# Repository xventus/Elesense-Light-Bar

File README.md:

# LAMP

Elesense Light Bar is a monitor lamp from [kickstarter](https://www.kickstarter.com/projects/elesense/elesense-computer-monitor-light-bar). Because of the need to control it using a web interface or script and also out of curiosity how it works, this project was created. Take a screwdriver and an anlyzer and see how it works.....  

<table>
    <tr>
        <td></td>
        <td></td>
        <td></td>
        <td></td>
    </tr>
</table>

## Hardware
For communication is to use LC12S module communicating on 2.4GHz. It is used as a transparetic serial line at 9600bps. 
For the control of the LAMP project the ESP32 module is used. The development was based on ESP-WROVER-KIT. 

[Wiring the lamp controller based on ESP32](https://github.com/xventus/Elesense-Light-Bar/blob/master/hw/schema.pdf) 

The first version of the board is made. Gerber is in the hw directory. 

[Interactive BOM](https://fotoventus.cz/lamp/ibom.html)

Still in development, custom PCB is being created, will be published in time. 

---
| ESP32 GPIO  | Note         |
|------------|---------------|
|   GPIO_NUM_25 | LSC12S TX |
|   GPIO_NUM_26 | LSC12S RX |
|   GPIO_NUM_19 | LSC12S SET |
|   GPIO_NUM_18 | LSC12S CS |
|   GPIO_NUM_2  | A BUTTON |
|   GPIO_NUM_4  | B BUTTON |
|   GPIO_NUM_0  | FLASH BUTTON |
|   GPIO_NUM_5  | HEART BEAT LED |

## Protocol

example: 

`0x53 0xC2 0x1C 0x00 0x9D 0x1B 0x00 0x0E 0x01 0x17 0x0E 0x26 0x00` 

---
| Byte position  | Note |
|------------|------------------------------------------------------------------------|
| 0          | header  (always 0x53)                                                  |
| 1          | lampID-1  (0xC2)                                                       |
| 2          | lampID-2  (0x1C)                                                       |
| 3          | lampID-3  (always 0x00)                                                |
| 4          | lampID-4  (0x9D)                                                       |
| 5          | lampID-5  (0x1B)                                                       |
| 6          | lampID-6 (always 0x00)                                                 |
| 7          | lampID-7  (0x0E) (if 0xA4 appears then the rest of the octet is 0x00)  |
| 8          | command  0x01 - ON,  0x10 - OFF, 0x02 - Automatic dimming       (0x01) |
| 9          |0x00 - 0x17 intensity (0x00 - min intensity, 0x17 - max intensity), note: when off  0x10 (0x17) |
| 10         |0x00 - 0x17 intensity (0x00 - Yellow MAX, 0x17 - Yellow Min), note: when off 0x10  ([0x0E)      | 
| 11         | Checksum  = Sum of [8] + [9] + [10]   (0x26)                                                   |
| 12         | END mark   (always 0x00)                                                                       |

## HTTP command

LAMP OFF command

`curl -X POST -H "Content-Type: application/json" -d '{"command": "OFF"}' http://xxx.xxx.xxx.xxx/command`

LAMP ON with intensity and hue command

`curl -X POST -H "Content-Type: application/json" -d '{"command": "ON","brightness":"17","hue":"12"}' http://xxx.xxx.xxx.xxx/command`

LAMP get ID & values

`curl http://192.168.2.222/values`

## HW Buttons

---
| Button     | Note |
|------------|------------------------------------------------------------------------|
| X-BOOT + reset |  Upoad firmware via serial 
| X-BOOT     |  ON / OFF |
| A     | Increasing the brightness intensity|
| B     | Decreasing the brightness intensity|
| A + B + reset | New initialization, creates a LAM AP and allows you to set up a new WiFi connection | 

## Programming and configuration

Note!!:  Resistor R10 is used on GPIO2, it is necessary to ground it during upload. Press the push button or insert the shorting jumper on the push button.

1. Connect ESP-LAM PCB via 3V3 USB-serial converter to J4 connector
2. Connect power via USB-C connector or via J1
3. Run VisualCode and upload the project
4. In VC Platformio run Build Sytem File Image
5. Press and hold the BTN-XBOOT button and press the RST button, then release RST and BTN-XBOOT 
7. In VC Platformio run Upload Sytem File Image
8. Press and hold the BTN-XBOOT button and press the RST button, then release RST and BTN-XBOOT
9. In VC Platformio, start the Upload Program to ESP
10. Press the RST button, then the LED should start flashing 
11. On your computer, search for the AP named LAMP AP and connect
12. In your web browser enter the address http://192.168.4.1
13. Configure the wifi network and select submit
14. After reboot, ESP-LAMP will connect to your wifi network and you can connect from the browser to the IP address received from DHCP or specified in the configuration and control the lamp.  

## LED STATE

---
| LED     | Note |
|------------|------------------------------------------------------------------------|
| .. .. .. |  LAMP runs in AP mode and waits for configuration |
| . -  . - |  The LAMP is waiting to be paired. Please use the original control for the lamp. ESP-LAMP will copy the lamp ID.   |
| - - - -  |  LAMP connected to wifi and works |
| . . . . .|  Error |

## Web interface

## Case

<table>
    <tr>
        <td></td>
        <td></td>
        <td></td>
        <td></td>
    </tr>
</table>

STL files to download for 3D printing of the box. Thanks to [Pavel Vanek](https://github.com/Bobik77)

[STL top part](case/ESP_Lamp_Top_V2.stl)

[STL bottom part](case/ESP_Lamp_Bottom_V2.stl)

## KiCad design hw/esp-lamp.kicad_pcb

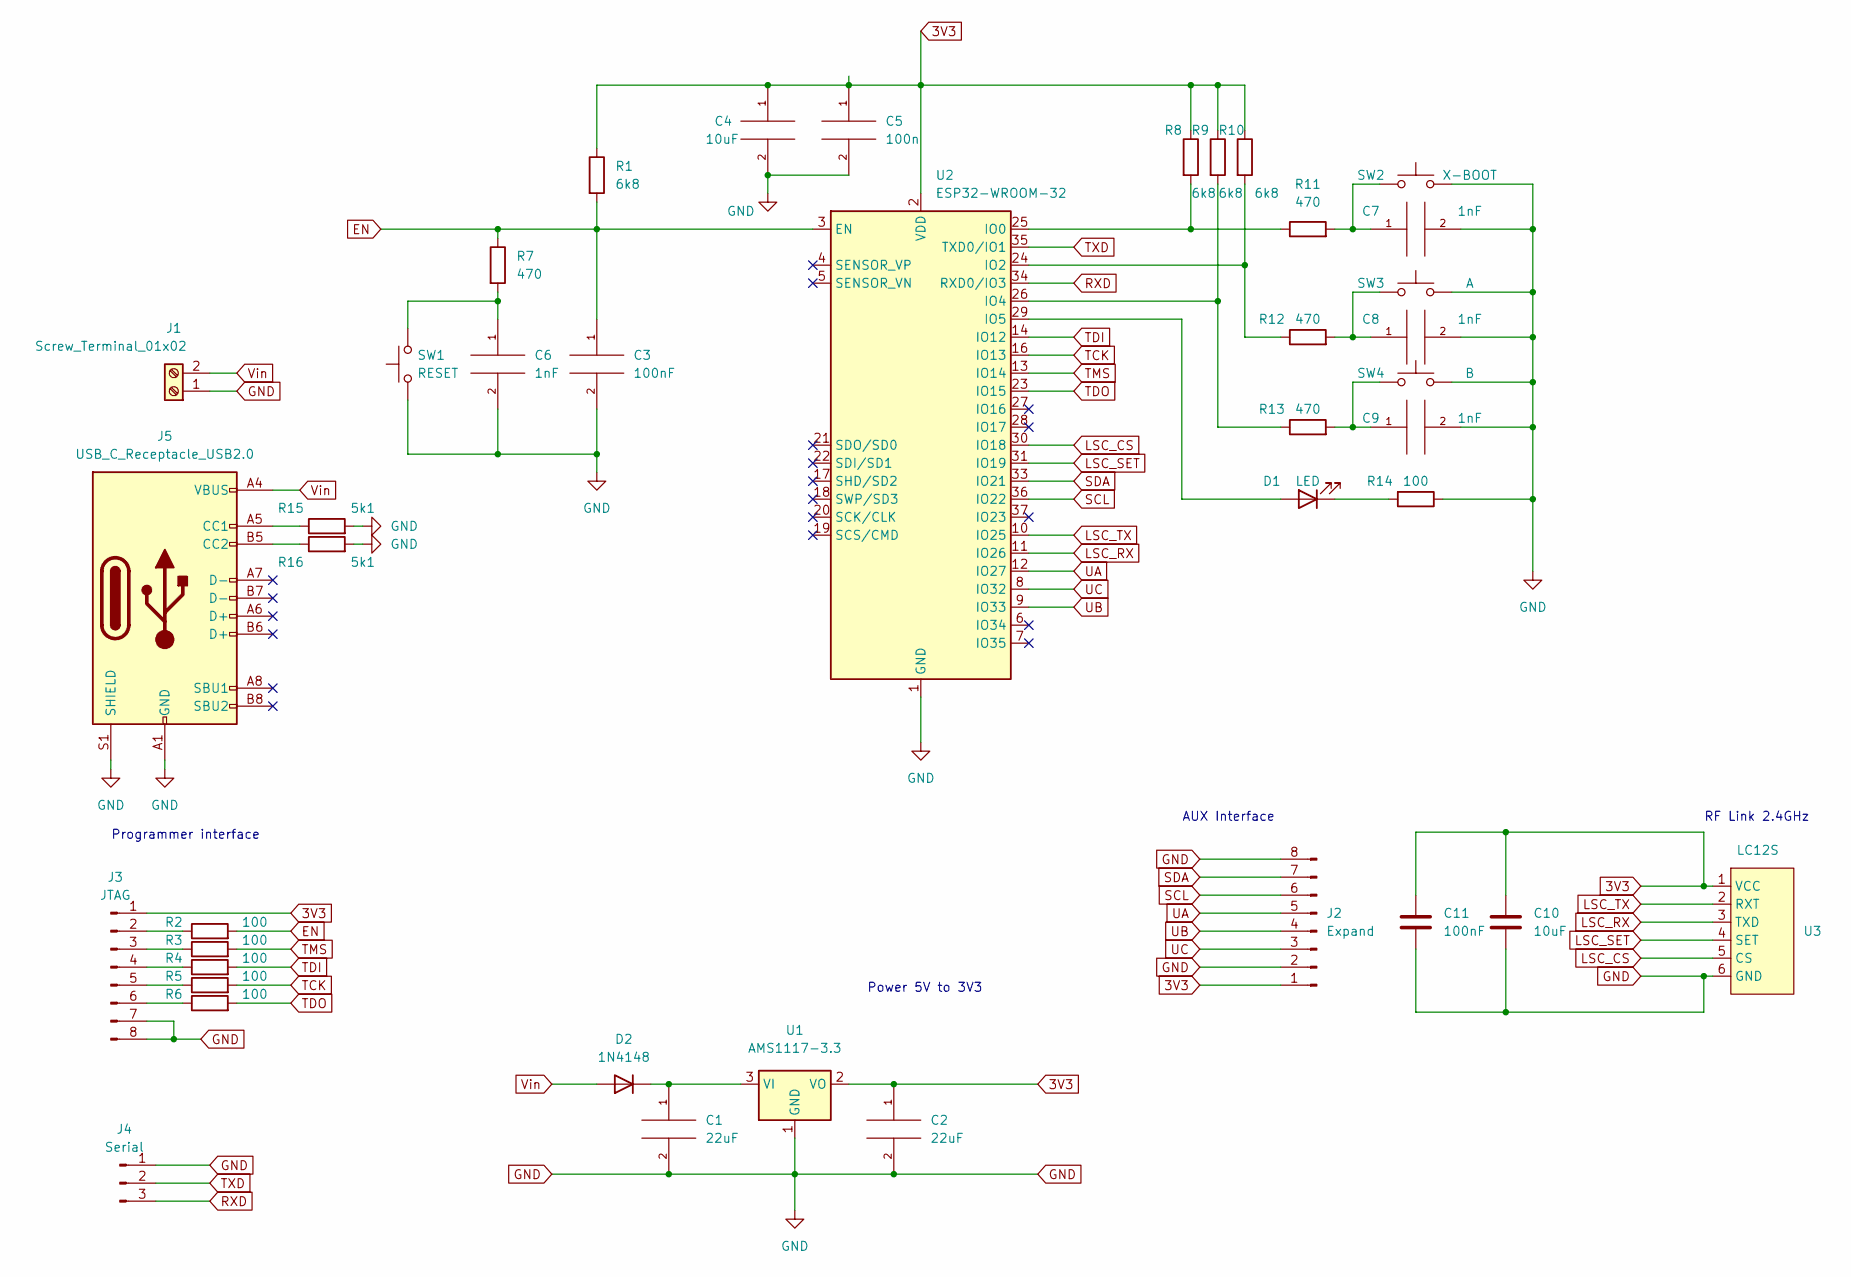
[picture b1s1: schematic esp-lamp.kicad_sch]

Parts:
C1, C2: 22uF; C_0603_1608Metric_Pad1.08x0.95mm_HandSolder
C3, C11: 100nF; C_0603_1608Metric_Pad1.08x0.95mm_HandSolder
C4, C10: 10uF; C_0603_1608Metric_Pad1.08x0.95mm_HandSolder
C5: 100n; C_0603_1608Metric_Pad1.08x0.95mm_HandSolder
C6, C7, C8, C9: 1nF; C_0603_1608Metric_Pad1.08x0.95mm_HandSolder
D1: LED; LED_0805_2012Metric_Pad1.15x1.40mm_HandSolder
D2: 1N4148; D_SOD-128
J1: Screw_Terminal_01x02; TerminalBlock_Phoenix_MPT-0,5-2-2.54_1x02_P2.54mm_Horizontal
J2: Expand; PinHeader_2x04_P2.54mm_Vertical
J3: JTAG; PinHeader_2x04_P2.54mm_Vertical
J4: Serial; PinHeader_1x03_P2.54mm_Vertical
J5: USB_C_Receptacle_USB2.0; USB_C_Receptacle_HRO_TYPE-C-31-M-12
R1, R8, R9, R10: 6k8; R_0603_1608Metric_Pad0.98x0.95mm_HandSolder
R2, R3, R4, R5, R6, R14: 100; R_0603_1608Metric_Pad0.98x0.95mm_HandSolder
R7, R11, R12, R13: 470; R_0603_1608Metric_Pad0.98x0.95mm_HandSolder
R15, R16: 5k1; R_0603_1608Metric_Pad0.98x0.95mm_HandSolder
SW1: RESET; SW_PUSH_6mm_H4.3mm
SW2: X-BOOT; SW_PUSH-12mm_Wuerth-430476085716
SW3: A; SW_PUSH-12mm_Wuerth-430476085716
SW4: B; SW_PUSH-12mm_Wuerth-430476085716
U1: AMS1117-3.3; SOT-223-3_TabPin2
U2: ESP32-WROOM-32
U3: LC12S

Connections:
3V3: C2.1, C4.1, C5.1, C10.1, C11.1, J2.1, J3.1, R1.1, R8.1, R9.1, R10.1, U1.2 (VO), U2.2 (VDD), U3.1 (VCC)
EN: C3.1, R1.2, R2.2, R7.1, U2.3 (EN)
GND: C1.2, C2.2, C3.2, C4.2, C5.2, C6.2, C7.2, C8.2, C9.2, C10.2, C11.2, J1.1, J2.2, J2.8, J3.7, J3.8, J4.1, J5.A1 (GND), J5.A12 (GND), J5.B1 (GND), J5.B12 (GND), J5.S1 (SHIELD), R14.1, R15.2, R16.2, SW1.1, SW2.2, SW3.2, SW4.2, U1.1 (GND), U2.1 (GND), U2.15 (GND), U2.38 (GND), U2.39 (GND), U3.6 (GND)
LSC_CS: U2.30 (IO18), U3.5 (CS)
LSC_RX: U2.11 (IO26), U3.3 (TXD)
LSC_SET: U2.31 (IO19), U3.4 (SET)
LSC_TX: U2.10 (IO25), U3.2 (RXT)
unnamed: C6.1, R7.2, SW1.2
unnamed: C7.1, R11.2, SW2.1
unnamed: C8.1, R12.2, SW3.1
unnamed: C9.1, R13.2, SW4.1
unnamed: D1.2 (A), U2.29 (IO5)
unnamed: D1.1 (K), R14.2
unnamed: C1.1, D2.1 (K), U1.3 (VI)
unnamed: J3.2, R2.1
unnamed: J3.3, R3.1
unnamed: J3.4, R4.1
unnamed: J3.5, R5.1
unnamed: J3.6, R6.1
unnamed: J5.A5 (CC1), R15.1
unnamed: J5.B5 (CC2), R16.1
unnamed: R8.2, R11.1, U2.25 (IO0)
unnamed: R10.2, R12.1, U2.24 (IO2)
unnamed: R9.2, R13.1, U2.26 (IO4)
RXD: J4.3, U2.34 (RXD0/IO3)
SCL: J2.6, U2.36 (IO22)
SDA: J2.7, U2.33 (IO21)
TCK: R5.2, U2.16 (IO13)
TDI: R4.2, U2.14 (IO12)
TDO: R6.2, U2.23 (IO15)
TMS: R3.2, U2.13 (IO14)
TXD: J4.2, U2.35 (TXD0/IO1)
UA: J2.5, U2.12 (IO27)
UB: J2.4, U2.9 (IO33)
UC: J2.3, U2.8 (IO32)
Vin: D2.2 (A), J1.2, J5.A4 (VBUS), J5.A9 (VBUS), J5.B4 (VBUS), J5.B9 (VBUS)

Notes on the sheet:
AUX Interface
Power 5V to 3V3
Programmer interface
RF Link 2.4GHz

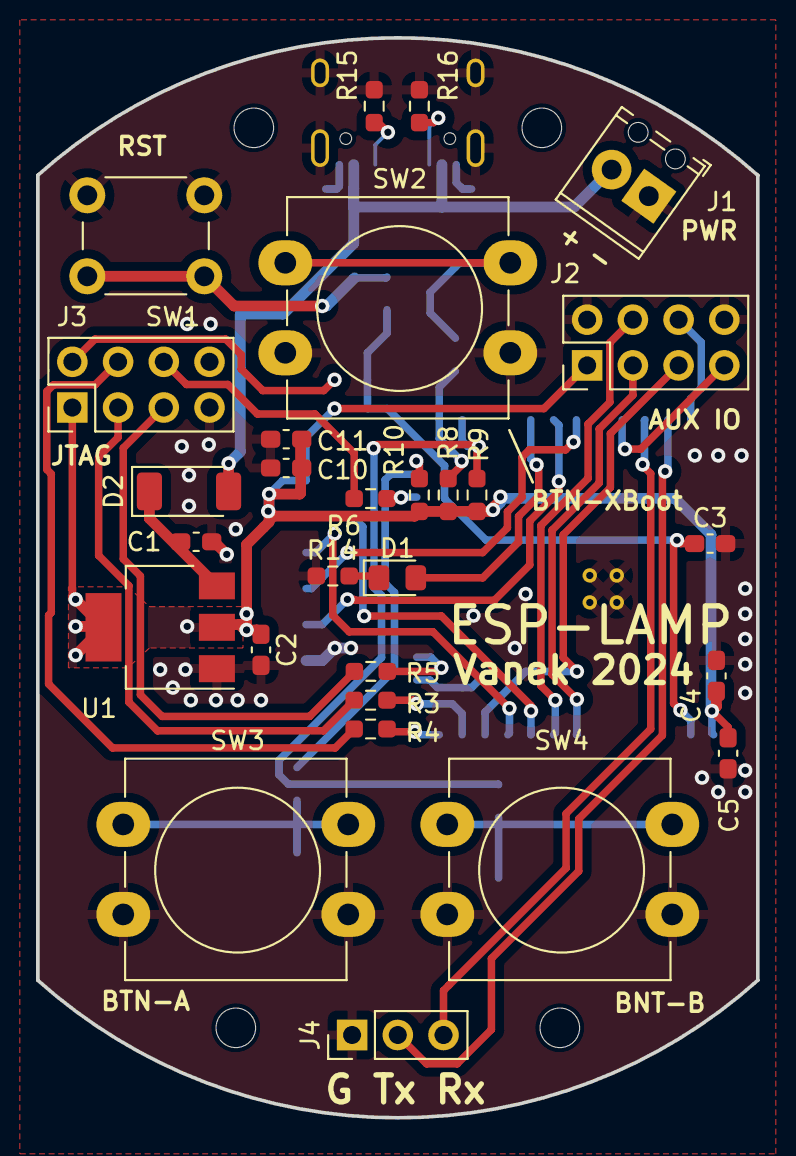
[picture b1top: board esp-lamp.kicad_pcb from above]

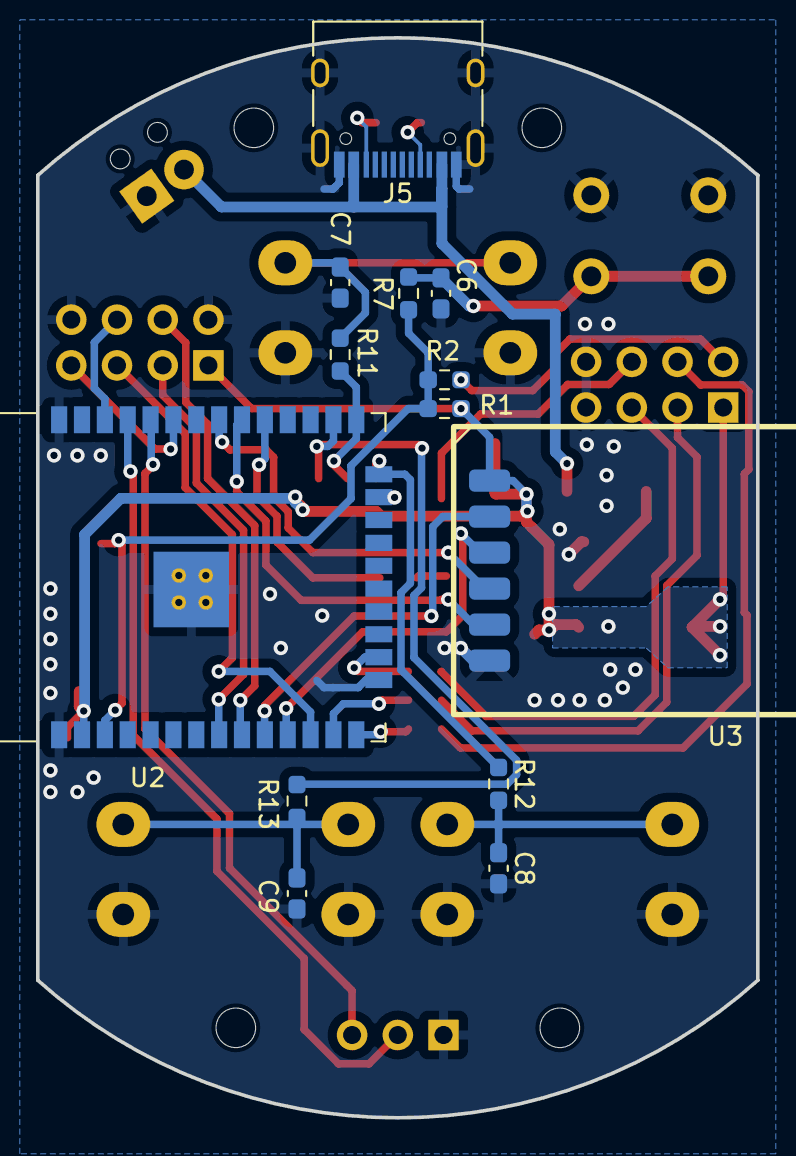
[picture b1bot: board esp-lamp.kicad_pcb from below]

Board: 2 copper layers, 40.0 x 60.0 mm, 41 parts (13 on the bottom side), 36 nets.

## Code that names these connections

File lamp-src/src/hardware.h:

//
// vim: ts=4 et
// Copyright (c) 2023 Petr Vanek, petr@fotoventus.cz
//
/// @file   hardware.h
/// @author Petr Vanek

#pragma once

#include "driver/gpio.h"
#include "driver/uart.h"

/**
 * @brief Hardware definition, pin assignment, communication interfaces settings
 * 
 */


// LEDs
#define  HEART_BEAT_LED  GPIO_NUM_5

// Buttons
#define  FLASH_BUTTON    GPIO_NUM_0
#define  A_BUTTON        GPIO_NUM_2
#define  B_BUTTON        GPIO_NUM_4

// Serial line to LSC12C
#define LSC_TX_PIN  GPIO_NUM_25 // connect to RX on LSC12C
#define LSC_RX_PIN  GPIO_NUM_26 // connect to TX pin on LSC12C
#define LSC_SET     GPIO_NUM_19 // set mode 
#define LSC_CS      GPIO_NUM_18 // chip select

// USED UART
#define LCS_UART    UART_NUM_1

// Aux free pins - not used 
#define I2C_SDA GPIO_NUM_21
#define I2C_SCL GPIO_NUM_22
#define UA_PIN  GPIO_NUM_27
#define UB_PIN  GPIO_NUM_33
#define UC_PIN  GPIO_NUM_32

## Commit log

2023-12-13 initial
2023-12-13 GPIO changed, html debouncing
2023-12-13 web example
2023-12-14 Update README.md http commands
2024-01-02 added hardware - schema idea & fix server allocation
2024-01-17 finalize pcb
2024-01-17 schema - pdf
2024-01-17 BOM updated
2024-02-09 changed upload via serial line
2024-02-10 added button task
2024-02-14 case
2024-02-18 Saving parameters to the light when switching off with the HW button.
2024-02-21 cover variant with LED shading
